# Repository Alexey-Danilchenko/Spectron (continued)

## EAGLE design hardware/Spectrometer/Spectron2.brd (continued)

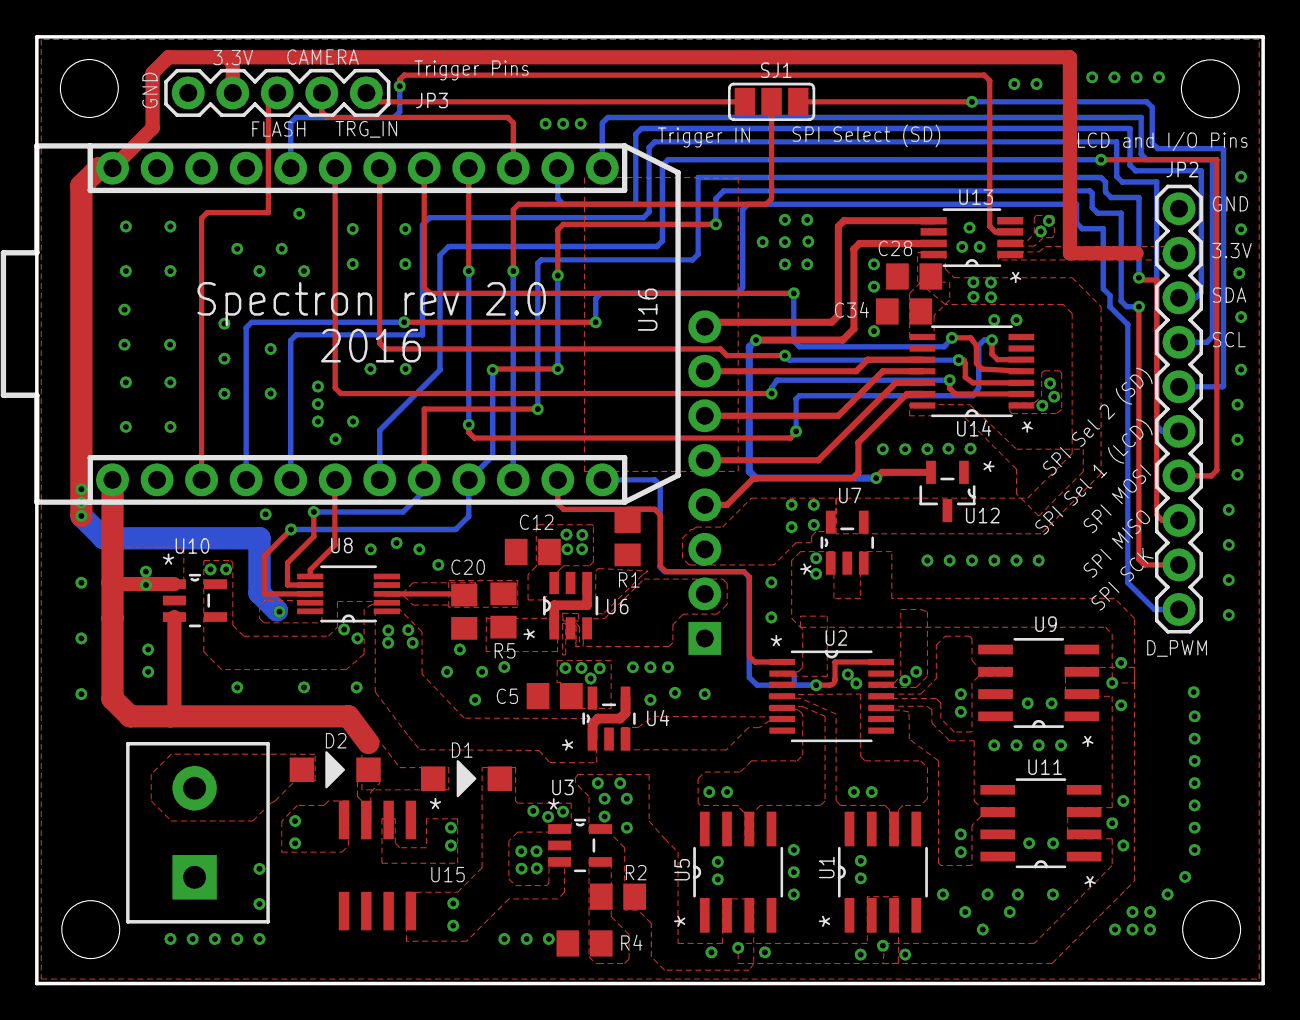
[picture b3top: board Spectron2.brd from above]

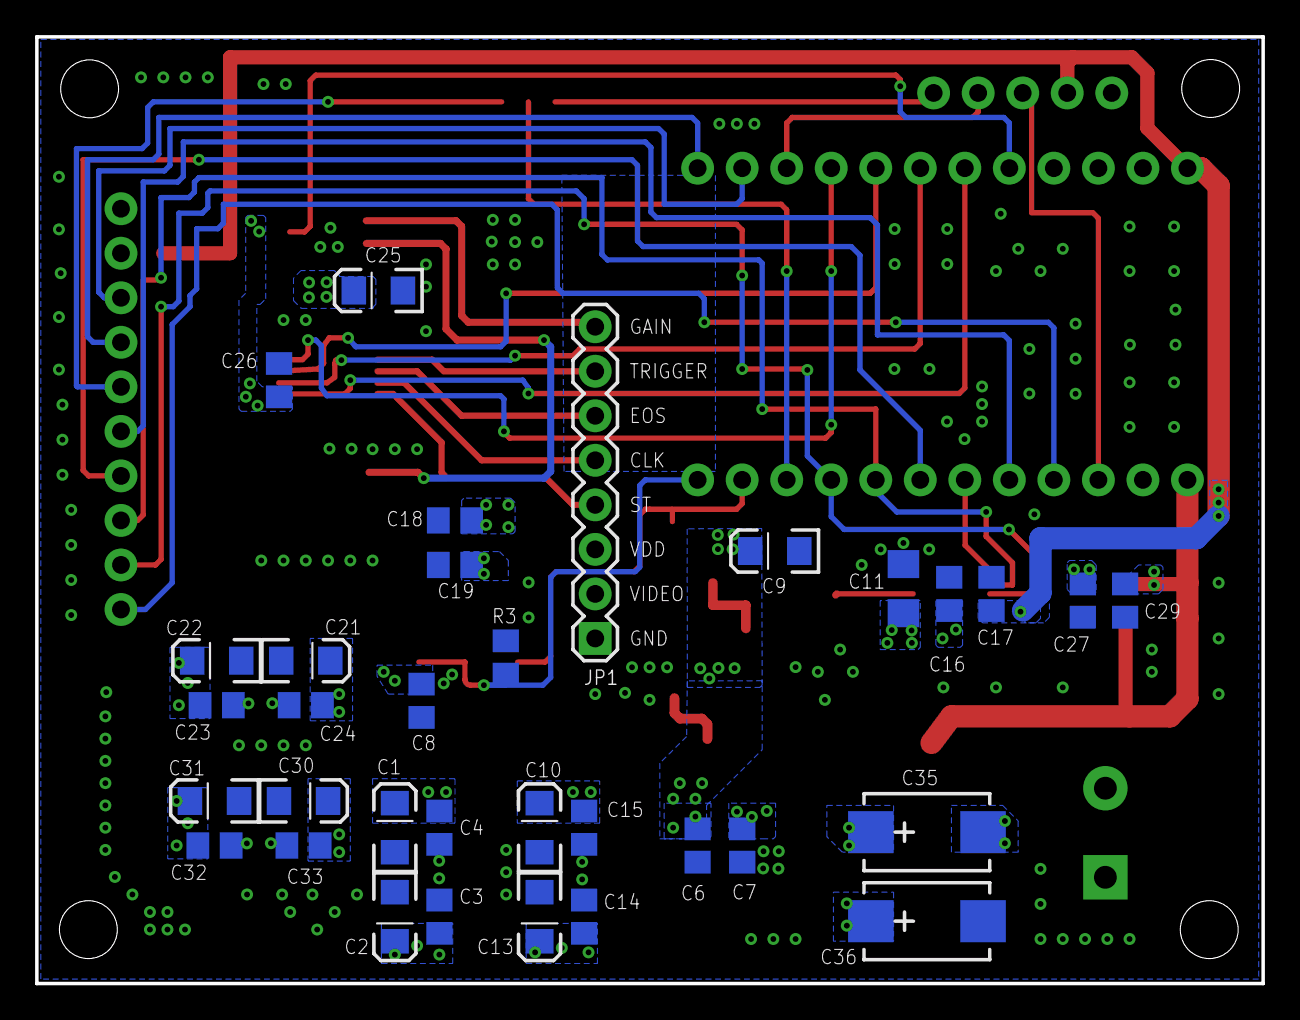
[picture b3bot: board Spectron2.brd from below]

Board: 2 copper layers, 70.0 x 54.0 mm, 69 parts (33 on the bottom side), 47 nets.

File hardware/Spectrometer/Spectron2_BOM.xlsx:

Qty | Value | Device | Package | Parts | Description | MPN | SUPPLIER | Distributor | Distributor Part Number
4 | 1uF | TANT-CAP1206 | EIA3216 | C1, C10, C21, C30 | Tantalum Capacitors - Solid SMD 1uF 25volts 10% A case Molded | 593D105X9025A2TE3 | Vishay | Mouser | 74-593D105X9025A2TE3
1 | 22uF | C-EUC0805 | C0805 | C11 | Multilayer Ceramic Capacitors MLCC - SMD/SMT 0805 22uF 25volts X5R 20% | GRM21BR61E226ME44L | Murata | Mouser | 81-GRM21BR61E226ME4L
6 | 10uF | C-EUC0805 | C0805 | C6, C7,C18, C19, C27, C29 | Multilayer Ceramic Capacitors MLCC - SMD/SMT 0805 10uF 35volts *Derate Voltage/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 | GRM21BC71E106KE11L | Murata | Mouser | 81-GRM21BC8YA106KE1L
1 | 2.7 nF | C-EUC0805 | C0805 | C20 | Multilayer Ceramic Capacitors MLCC - SMD/SMT 0805 2700pF 25volt X7R +/-10% | GRM216R71E272KA01D | Murata | Mouser | 81-GRM216R71E272KA1D
17 | 0.1uF | C-EUC0805 | C0805 | C3, C4, C8, C12, C14, C15, C16, C17, C23, C24, C26, C28, C32, C33, C34 and C1, 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 | Multilayer Ceramic Capacitors MLCC - SMD/SMT 0805 0.1uF 25volts X7R 10% | GRM21BR71E104KA01L | Murata | Mouser | 81-GRM40X104K25L
2 | 47uF | CPOL-USCT7343 | CT7343 | C35, C36 | Tantalum Capacitors - Polymer SMD 35volts 47uF 20% ESR=30mohms | T521X476M035ATE030 | Kemet | Mouser | 80-T521X476M35ATE30
1 | 1uF | C-EUC0805 | C0805 | C5 | Multilayer Ceramic Capacitors MLCC - SMD/SMT | GRM21BR71H105KA12K | Murata | Mouser | 81-GRM21BR71H105KA2K
6 | 10uF | TANT-CAP1206 | EIA3216 | C2, C9, C13, C22, C25, C31 | Tantalum Capacitors - Solid SMD 10UF 25V 10% | F951E106KAAAQ2 | AVX | Mouser | 647-F951E106KAAAQ2
2 | PMEG2010ER | DIODE-SOD123 | SOD123 | D1, D2 | Schottky Diodes & Rectifiers SCHOTTKY LOW VF | PMEG2010ER,115 | NXP | Mouser | 771-PMEG2010ER115
3 | 10K | R-EU_R0805 | R0805 | R1, R2, R3 | Thick Film Resistors - SMD 1/8watt 10Kohms 1% 100ppm | CRCW080510K0FKEA | Vishay | Mouser | 71-CRCW0805-10K-E3
1 | 20K | R-EU_R0805 | R0805 | R4 | Thick Film Resistors - SMD 1/8watt 20Kohms 1% 100ppm | CRCW080520K0FKEA | Vishay | Mouser | 71-CRCW0805-20K-E3
1 | 20 R | R-EU_R0805 | R0805 | R5 | Thick Film Resistors - SMD 0805 20ohm 1% Anti Surge AEC-Q200 | ESR10EZPF20R0 | ROHM Semiconductor | Mouser | 755-ESR10EZPF20R0
1 | AD7980 | AD7980 |  | U8 | Analog to Digital Converters - ADC 16-Bit 1 MSPS | AD7980ARMZ | Analog Devices | Mouser | 584-AD7980ARMZR7
1 | AD8031 | AD8031 |  | U4 | Operational Amplifiers - Op Amps 2.7V 800uA 80Mhz RRIO SGL | AD8031ARTZ-REEL7 | Analog Devices | Mouser | 584-AD8031ARTZ-R7
1 | ADA4841 | ADA4841 |  | U6 | Operational Amplifiers - Op Amps Low Power Low Noise and Distort RRO | ADA4841-1YRJZ-R7 | Analog Devices | Mouser | 584-ADA4841-1YRJZ-R7
1 | ADG1604 | ADG1604 |  | U2 | Multiplexer Switch ICs 4:1 19MHz 950 mOhm CMOS | ADG1604BRUZ | Analog Devices | Mouser | 584-ADG1604BRUZ-R7
1 | ADG3304 | ADG3304 |  | U14 | Translation - Voltage Levels Low VTG 1.15V-5.5V 4-CH Bidirect Logic | ADG3304BRUZ-REEL7 | Analog Devices | Mouser | 584-ADG3304BRUZ-R7
1 | ADG821 | ADG821 |  | U13 | Analogue Switch ICs 500mOhm 5.5V CMOS Dual SPST | ADG821BRMZ-REEL7 | Analog Devices | Mouser | 584-ADG821BRMZ-R7
1 | ADP7142-2.5 | ADP7142 |  | U10 | LDO Voltage Regulators 40V 200mA LDO 2.5Vo | ADP7142AUJZ-2.5-R7 | Analog Devices | Mouser | 584-ADP7142AUJZ2.5R7
2 | ADP7142-5.0 | ADP7142 |  | U3, U7 | LDO Voltage Regulators 40V 200mA LDO 5.0Vo | ADP7142AUJZ-5.0-R7 | Analog Devices | Mouser | 584-ADP7142AUJZ5.0R7
1 | LM2662 | LM2662 |  | U15 | Voltage Regulators - Switching Regulators Switched Capacitor Vtg Cnvtr | LM2662MX/NOPB | Texas Instruments | Mouser | 926-LM2662MX/NOPB
1 | REF192 | REF192 |  | U1 | Voltage References 2.5V Prec Micropwr LDO Low VRef | REF192GSZ | Analog Devices | Mouser | 584-REF192GSZ-R7
1 | REF193 | REF193 |  | U5 | Voltage References 3V Prec Micropwr LDO | REF193GSZ | Analog Devices | Mouser | 584-REF193GSZ
1 | REF195 | REF195 |  | U11 | Voltage References 5V Prec Micropwr LDO Low VRef | REF195GSZ | Analog Devices | Mouser | 584-REF195GSZ-R
1 | REF198 | REF198 |  | U9 | Voltage References 4.096V Prec Micropwr LDO Low VRef | REF198GSZ | Analog Devices | Mouser | 584-REF198GSZ-R
1 | TLV809 | TLV809 |  | U12 | Supervisory Circuits 3Pin Supply Vltg Sup | TLV809K33DBVR | Texas Instruments | Mouser | 595-TLV809K33DBVR
1 | C12666/C12880 | Preci-Dip 350-80-108-00-006101 |  | JP1 | Header 8 | 714-87-112-31-012101 | Preci-Dip | RS-Online | 702-0060
1 | Trigger Pins | M05PTH | 1X05 | JP3 | Header 5
1 | POWERSUPPLY DC21MMX | POWERSUPPLY DC21MMX | POWERSUPPLY_DC-21MM | DC1 | DC Power Connectors Power Jacks | PJ-102AH | CUI Inc. | Mouser | 490-PJ-102AH
1 | PHOTON without headers | PHOTON without headers | PHOTON | U16 |  |  |  | Mouser
4 | Photon socket, sensor board socket | Preci-Dip 714-87-112-31-012101 |  |  |  | 714-87-112-31-012101 | Preci-Dip | DIGIKEY | 1212-1166-ND
2 | Photon headers for the sockets above | Preci-Dip 350-80-112-00-006101 |  |  |  | 350-80-112-00-006101, 350-PP-1NN-00-006101 series | Preci-Dip | RS-Online | 702-0095
1 | Spectrometer stand | MICRO SPECTROMETER |  |  | Hamamatsu Micro-Spectrometer C12666MA or C12880MA, part ordered is Preci-Dip st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 | 115-87-314-41-003101 | Preci-Dip | DIGIKEY | 1212-1045-ND

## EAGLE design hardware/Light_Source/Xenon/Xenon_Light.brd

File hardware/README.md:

# Hardware

All the custom made circuits and boards were designed in [Cadsoft Eagle](http://www.autodesk.com/products/eagle/overview). All components for these were separated into standalone Eagle library for easier access. 

__Note:__ All the boards were tuned up for making with [OSH Park](https://oshpark.com/) - all relevant DRC and ERC rule checks were therefore applied an validated.

This project has the following several distinct and standalone components:

* [Spectrometer](Spectrometer) - board controlling spectrometer and performing spectral measurements
* [Stepper Motor Control](Motor) - board driving stepper motor for automating monochromator operation
* [Light Sources](Light_Source) - selection of controllable light sources providing input for monochromator

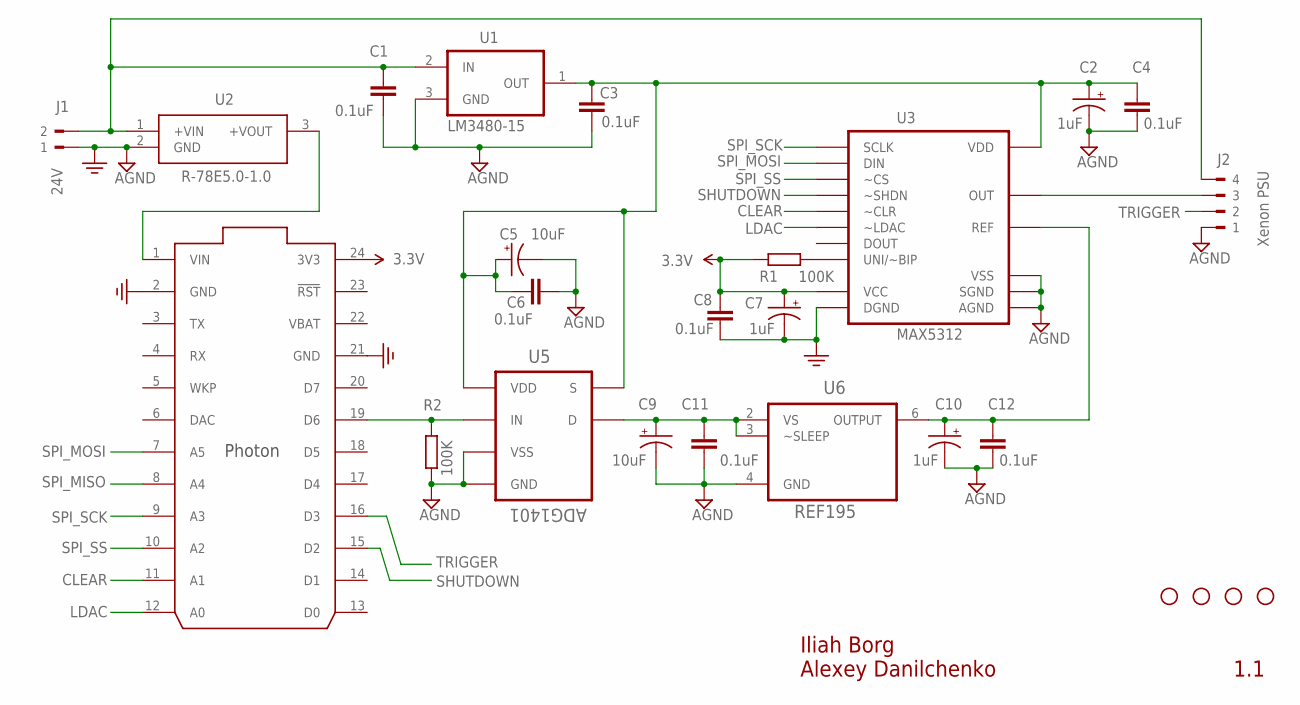
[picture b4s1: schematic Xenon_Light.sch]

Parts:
C1, C3, C4, C6, C8, C11, C12: 0.1uF; C0805
C2, C7, C10: 1uF; EIA3216
C5, C9: 10uF; EIA3216
J1: 24V; WEIDMULLER_PM5.08_2
J2: Xenon PSU; TERMINAL_BLK_4X5MM
R1, R2: 100K; R0805
STANDOFF1, STANDOFF2, STANDOFF3, STANDOFF4: STAND-OFF
U1: LM3480-15; SOT23
U2: R-78E5.0-1.0
U3: MAX5312; SSOP16
U4: PHOTON_WITH_HEADERS; PHOTON
U5: ADG1401; SOP65P490X110-8N
U6: REF195; SOIC127P600X175-8N

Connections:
3.3V: C7.A (+), C8.2, R1.2, U3.6 (VCC), U4.24 (3V3)
15V: C9.A (+), C11.2, U5.8 (D), U6.2 (VS), U6.3 (~SLEEP)
CLEAR: U3.15 (~CLR), U4.11 (A1)
GND: C1.1, C2.C (-), C3.1, C4.1, C5.C (-), C6.1, C7.C (-), C8.1, C9.C (-), C10.C (-), C11.1, C12.1, J1.1, J2.1, R2.1, U1.3 (GND), U2.2 (GND), U3.5 (DGND), U3.10 (SGND), U3.11 (AGND), U3.12 (VSS), U4.2 (GND), U4.21 (GND), U5.3 (GND), U5.7 (VSS), U6.4 (GND)
LDAC: U3.16 (~LDAC), U4.12 (A0)
unnamed: C1.2, J1.2, J2.4, U1.2 (IN), U2.1 (+VIN)
unnamed: U2.3 (+VOUT), U4.1 (VIN)
unnamed: R2.2, U4.19 (D6), U5.6 (IN)
unnamed: R1.1, U3.8 (UNI/~BIP)
unnamed: J2.3, U3.9 (OUT)
REF: C10.A (+), C12.2, U3.13 (REF), U6.6 (OUTPUT)
SHUTDOWN: U3.7 (~SHDN), U4.15 (D2)
SPI_MISO: U4.8 (A4)
SPI_MOSI: U3.2 (DIN), U4.7 (A5)
SPI_SCK: U3.1 (SCLK), U4.9 (A3)
SPI_SS: U3.3 (~CS), U4.10 (A2)
TRIGGER: J2.2, U4.16 (D3)
V15V: C2.A (+), C3.2, C4.2, C5.A (+), C6.2, U1.1 (OUT), U3.14 (VDD), U5.1 (S), U5.4 (VDD)
VBAT: U4.22 (VBAT)

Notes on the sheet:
1.1
Iliah Borg Alexey Danilchenko

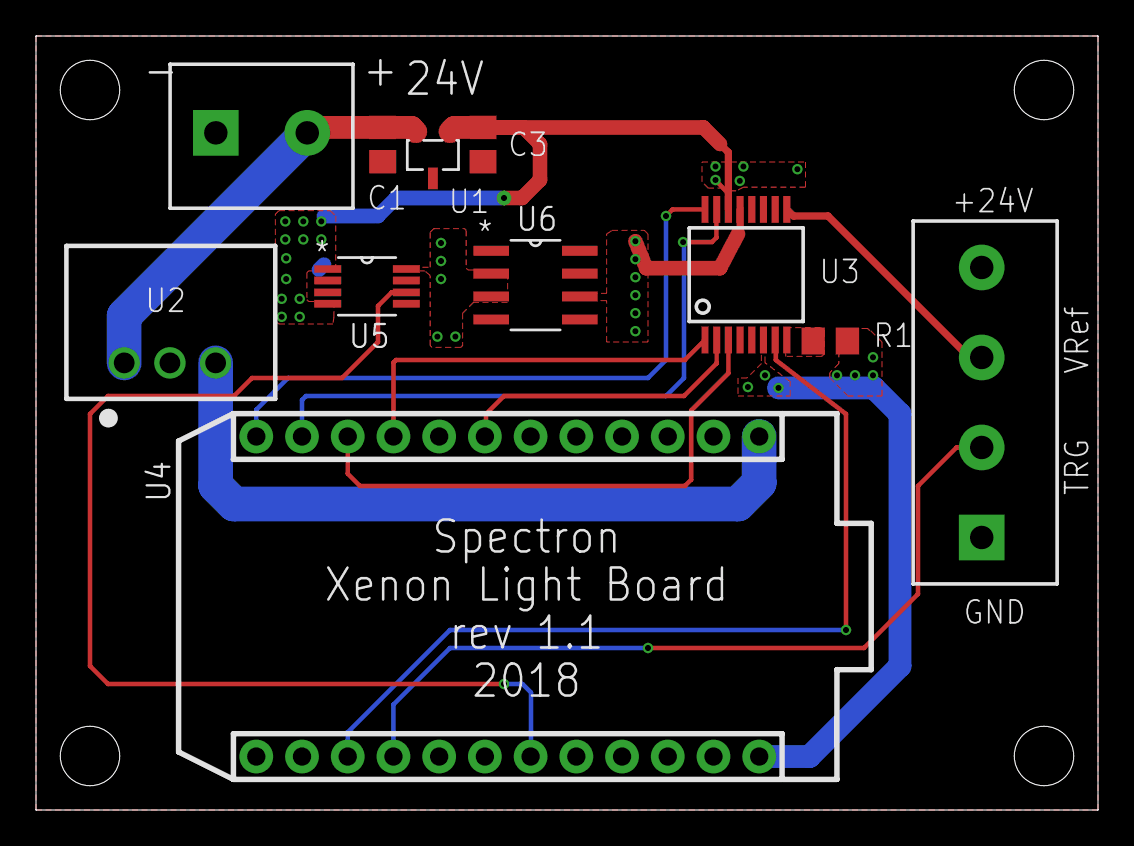
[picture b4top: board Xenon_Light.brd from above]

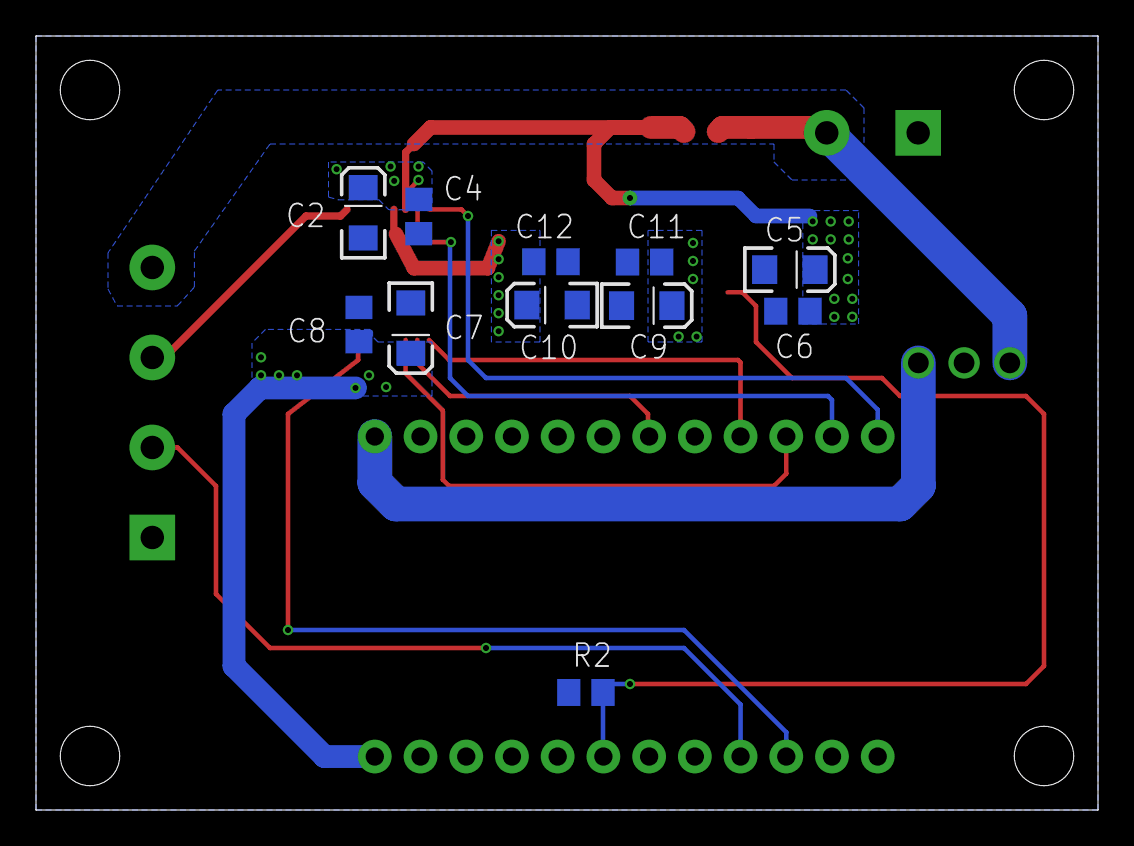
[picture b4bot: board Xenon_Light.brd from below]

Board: 2 copper layers, 59.0 x 43.0 mm, 26 parts (11 on the bottom side), 17 nets.

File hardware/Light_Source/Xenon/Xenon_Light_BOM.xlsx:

Qty | Value | Device | Package | Parts | Description | MPN | SUPPLIER | Distributor | Distributor Part Number
3 | 1uF | TANT-CAP1206 | EIA3216 | C2, C7, C10 | Tantalum Capacitors - Solid SMD 1uF 35V 20% A case | TMCMA1V105MTRF | Vishay | Mouser | 74-TMCMA1V105MTRF
7 | 0.1uF | C-EUC0805 | C0805 | C1,C3,C4,C6,C8,C11,C12 | Multilayer Ceramic Capacitors MLCC - SMD/SMT CEU 0805 50V 0.1uF X7R 10% | CEU4J2X7R1H104K125AE | TDK | Mouser | 810-CEU4J2X7R1H104K
2 | 10uF | TANT-CAP1206 | EIA3216 | C5,C9 | Tantalum Capacitors - Solid SMD 25V 10uF 20% 1206 ESR= 2 Ohms | F951E106MAAAQ2 | AVX | Mouser | 647-F951E106MAAAQ2
2 | 100K | R-EU_R0805 | R0805 | R1, R2 | Thick Film Resistors - SMD Thick Film Resistors - SMD 0805 100Kohms 5% AEC-Q200 | ERJ-6GEYJ104V | Panasonic | Mouser | 667-ERJ-6GEYJ104V
1 | LM3480-15 | LM3480 | SOT23 | U1 | LDO Voltage Regulators 100mA Quasi LDO Linear Vtg Reg | LM3480IM3X-15/NOPB | Texas Instruments | Mouser | 926-LM3480IM3X15NOPB
1 | R-78E5.0-1.0 | R-78E5.0-1.0 | R-78E5.0-1.0 | U2 | Non-Isolated DC/DC Converters 8-28Vin 5V 1.0A THRU | R-78E5.0-1.0 | RECOM Power | Mouser | 919-R-78E5.0-1.0
1 | MAX5312 | MAX5312 | SSOP16 | U3 | Digital to Analog Converters - DAC 12-Bit Precision DAC | MAX5312EAE+ | Maxim Integrated | Mouser | 700-MAX5312EAE
1 | ADG1401 | ADG1401BRMZ | SOP65P490X110-8N | U5 | Analogue Switch ICs IC 1 Ohm 16.5V iCMOS SPST | ADG1401BRMZ | Analog Devices | Mouser | 584-ADG1401BRMZ
1 | REF195 | REF195 | SOIC127P600X175-8N | U6 | Voltage References 5V Prec Micropwr LDO Low VRef | REF195GSZ | Analog Devices | Mouser | 584-REF195GSZ-R
1 | PHOTON without headers | PHOTON without headers | PHOTON | U4 |  |  |  | Mouser
2 | Photon socket | Preci-Dip 714-87-112-31-012101 |  |  |  | 714-87-112-31-012101 | Preci-Dip | DIGIKEY | 1212-1166-ND
2 | Photon headers for the sockets above | Preci-Dip 350-80-112-00-006101 |  |  |  | 350-80-112-00-006101, 350-PP-1NN-00-006101 series | Preci-Dip | RS-Online | 702-0095
1 | Xenon PSU | Terminal Block |  | J2 | 5mm Pitch Straight, PCB Terminal Block, PCB Mount, 4 Way | 897-0856 | RS Pro | RS-Online | 897-0856
1 | +24V | Terminal Block |  | J1 | 5mm Pitch Straight, PCB Terminal Block, PCB Mount, 2 Way | 282836-2 | TE Connectivity | RS-Online | 361-7667

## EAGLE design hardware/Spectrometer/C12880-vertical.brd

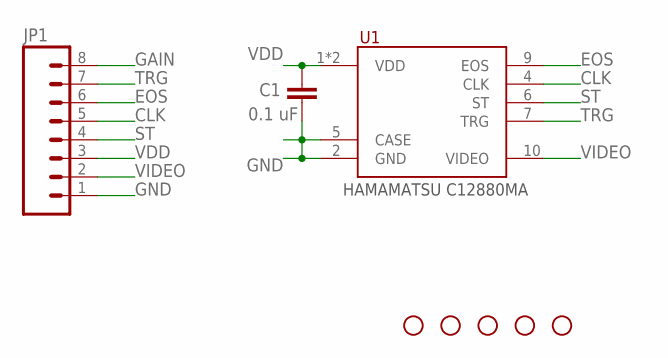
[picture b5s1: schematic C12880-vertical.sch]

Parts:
C1: 0.1 uF; C0805
JP1: M08SILK_FEMALE_PTH; 1X08
STANDOFF1, STANDOFF2, STANDOFF3, STANDOFF4, STANDOFF5: STAND-OFF
U1: MICROSPEC-C12880MA; C12880MA

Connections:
CLK: JP1.5, U1.4 (CLK)
EOS: JP1.6, U1.9 (EOS)
GAIN: JP1.8
GND: C1.2, JP1.1, U1.2 (GND), U1.5 (CASE)
ST: JP1.4, U1.6 (ST)
TRG: JP1.7, U1.7 (TRG)
VDD: C1.1, JP1.3, U1.1 (VDD), U1.3 (VDD)
VIDEO: JP1.2, U1.10 (VIDEO)

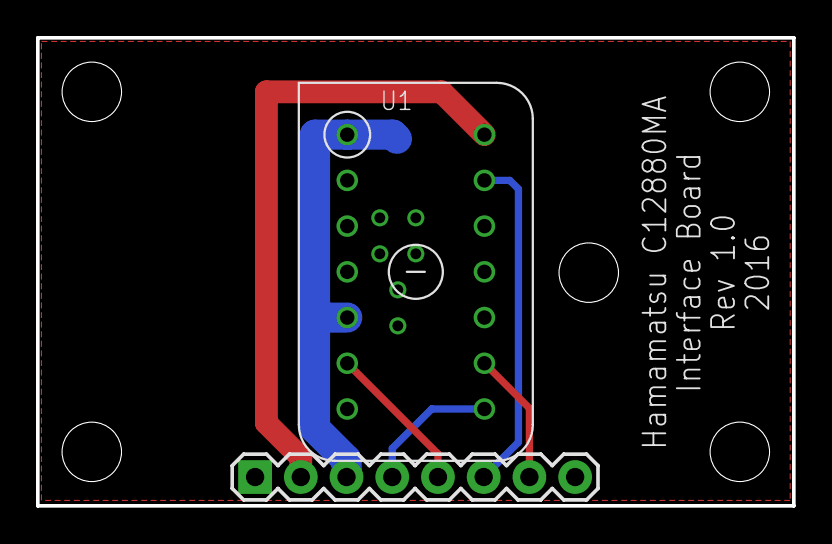
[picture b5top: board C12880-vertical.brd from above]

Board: 2 copper layers, 42.0 x 26.0 mm, 8 parts (1 on the bottom side), 7 nets.

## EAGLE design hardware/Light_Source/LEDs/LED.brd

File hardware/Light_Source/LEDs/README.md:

# LED Light Source

The LED light source component uses [Yuji LEDs](https://store.yujiintl.com/). More specifically their VTC (CRI 98) LEDs in [COB package for 5600K](YJWJ040-1.0_YJ-VTC-135L-G01.pdf) correlated colour temperature. A package of 4xVTC LED COBs clustered together is used for this light source. For more technical details on individual COB specifications see [Yuji LED web store](https://store.yujiintl.com/collections/led-cobs/products/yujileds-cri-98-9w-cob-led-135l).

These LEDs were chosen for the broad spectrum coverage they provide. An example of spectral response captured from the LEDs used in this setup ([also available as .CSV file](VTC5600_spectrum.csv)):

This component consists of two distinct and connected parts - LED driver/controller board and LED light head assembly. The whole circuit requires +12V/5A DC power supply to operate.

The photo below gives a clearer idea of the asssembled setup:

### LED Driver Board

The LED driver/controller board is a standalone LED driver with PWM control and 4000:1 dimming ratios (programmatically controlled). The LED driver board has two constant current channels - each capable of driving 450mA LEDs with up to 50V. This setup uses 2x LED strings (one per each channels) with 2xLEDs in series in each string (4x LEDs in total).

The board has 4 pin PWM connector allowing to control LED heatsink fan (if it is used). It also features I2C temperature sensor connector for board/environment temperature monitoring (if used) and 1-Wire thermocouple interface connector for LED temperature monitoring (if used).

Board schematic is also [available as standalone PDF](LED.pdf). Bill of material [is available in Excel format](LED_BOM.xlsx).

The following are the board layouts available (generated by OSH Park preview):

### LED Light Head Assembly

This assembly utilises the board with connector to the main LED driver board and mechanical connectors to 4xVTC LED COBs mounted directly on heatsink. The board has square cutout that fits tightly around 2x2 layout of VTC LED COBs with metallic pins soldered to the board acting as mechanical connectors to the LEDs. This allows to keep LEDs and heatsink setup separate from the board and optical assembly for easier replacement of the parts. The LED COBs are connected in series of two per string. 

The LED COBs are glued to a heatsink directly with [Arctic Silver Thermal Adhesive](http://www.arcticsilver.com/arctic_silver_thermal_adhesive.htm) in a tightly formed cluster. In series connection for each pair is formed by direct wire soldering onto the LEDs. This photo illustrates the setup:

The board with soldered pins on top of LEDs mounted on heatsink as follows:

The board then has a range of holes to allow attachments of the reflector, condenser lens and holder. Below is the example of the fully assembled setup:

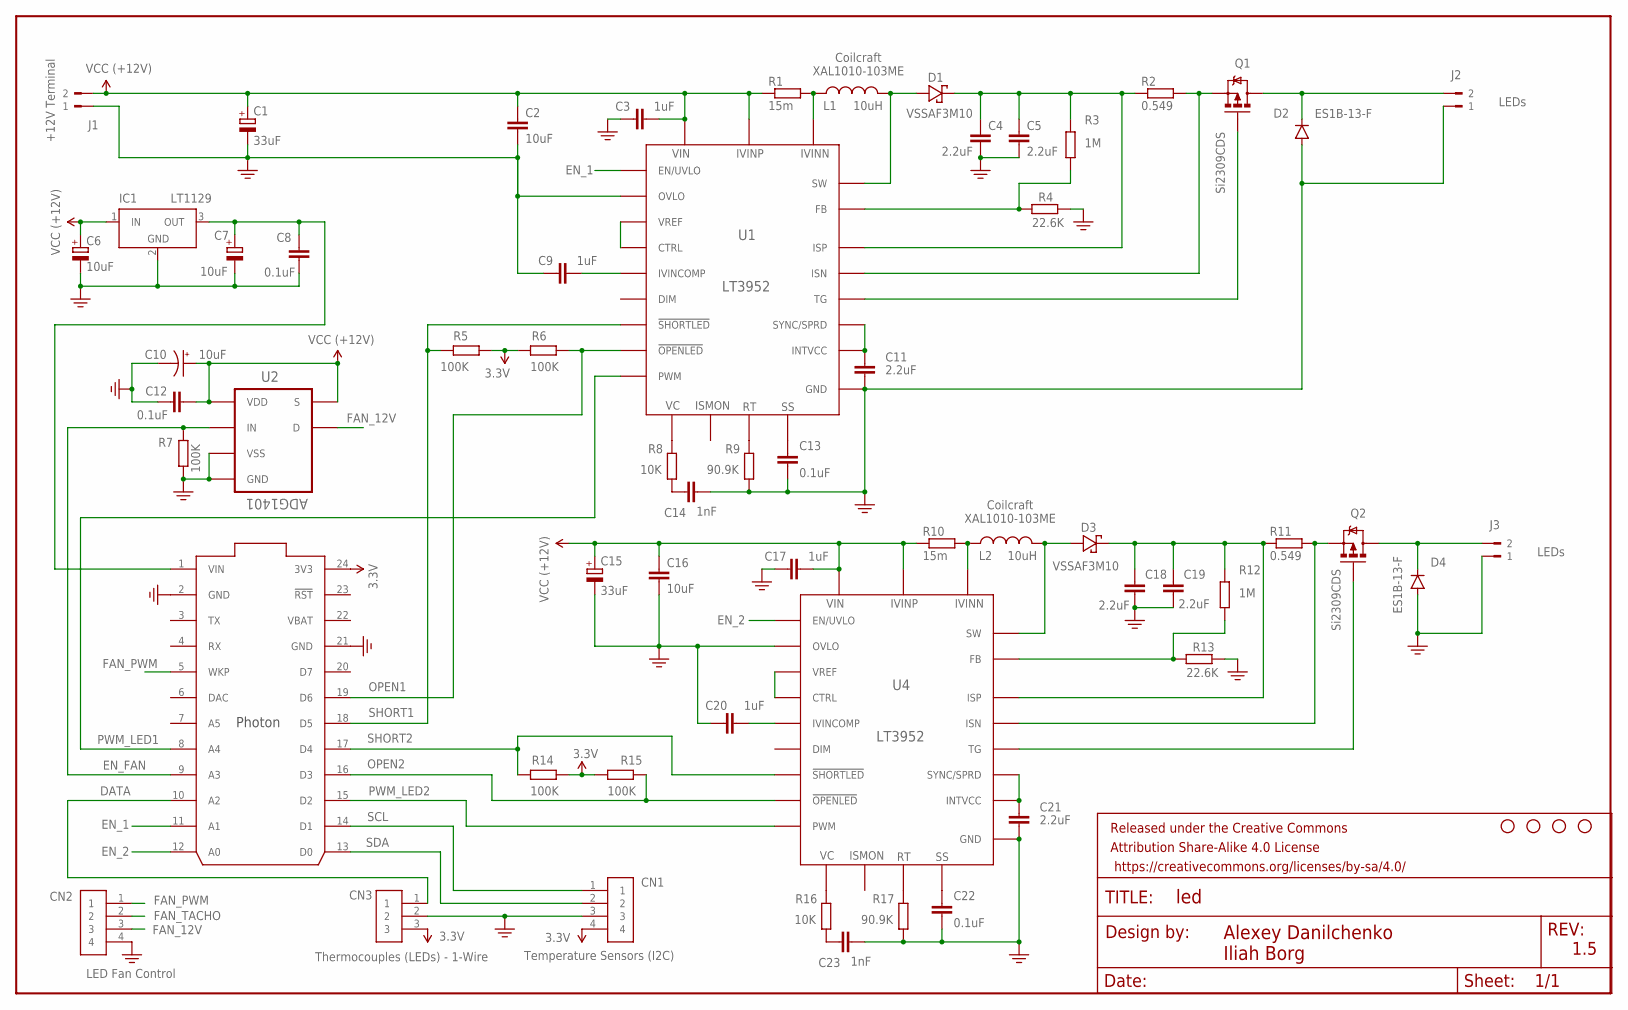
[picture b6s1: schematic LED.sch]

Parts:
C1, C15: 33uF; PANASONIC_E
C2, C16: 10uF; C1206
C3, C9, C17, C20: 1uF; C0805
C4, C5, C18, C19: 2.2uF; C1206
C6, C7: 10uF; CT7343
C8, C12, C13, C22: 0.1uF; C0805
C10: 10uF; EIA3216
C11, C21: 2.2uF; C0805
C14, C23: 1nF; C0805
CN1: Temperature Sensors (I2C); 1X04-BIG
CN2: LED Fan Control; 1X04-BIG
CN3: Thermocouples (LEDs) - 1-Wire; 1X03
D1, D3: VSSAF3M10; SODFL5226X100N
D2, D4: ES1B-13-F; SMA-DIODE_ALT
FRAME1: 1.0; CREATIVE_COMMONS
IC1: LT1129; SOT223
J1: +12V Terminal; WEIDMULLER_PM5.08_2
J2, J3: LEDs; WEIDMULLER_PM5.08_2
L1, L2: 10uH; XAL1010
Q1, Q2: Si2309CDS; SOT23-3
R1, R10: 15m; R1206
R2, R11: 0.549; R1206
R3, R12: 1M; R0805
R4, R13: 22.6K; R0805
R5, R6, R7, R14, R15: 100K; R0805
R8, R16: 10K; R0805
R9, R17: 90.9K; R0805
STANDOFF1, STANDOFF2, STANDOFF3, STANDOFF4: STAND-OFF
U1, U4: LT3952; TSSOP-28_FE/EB-M
U2: ADG1401; SOP65P490X110-8N
U3: PHOTON_WITH_HEADERS; PHOTON

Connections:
3.3V: CN1.4, CN3.3, R5.1, R6.2, R14.2, R15.1, U3.24 (3V3)
+5VDC: C7.+, C8.1, IC1.3 (OUT), U3.1 (VIN)
DATA: CN3.1, U3.10 (A2)
EN_1: U1.8 (EN/UVLO), U3.11 (A1)
EN_2: U3.12 (A0), U4.8 (EN/UVLO)
EN_FAN: R7.2, U2.6 (IN), U3.9 (A3)
FAN_12V: CN2.3, U2.8 (D)
FAN_PWM: CN2.1, U3.5 (WKP)
FAN_TACHO: CN2.2
GND: C1.-, C2.2, C3.2, C4.2, C5.2, C6.-, C7.-, C8.2, C9.2, C10.C (-), C11.2, C12.1, C13.2, C14.2, C15.-, C16.2, C17.2, C18.2, C19.2, C20.2, C21.2, C22.2, C23.2, CN1.3, CN2.4, CN3.2, D2.A, D4.A, IC1.2 (GND), IC1.4 (GND), J1.1, J2.1, J3.1, R4.1, R7.1, R9.1, R13.1, R17.1, U1.1 (GND), U1.9 (OVLO), U1.12 (GND), U1.28 (GND), U1.EPAD (GND), U2.3 (GND), U2.7 (VSS), U3.2 (GND), U3.21 (GND), U4.1 (GND), U4.9 (OVLO), U4.12 (GND), U4.28 (GND), U4.EPAD (GND)
unnamed: L1.1, R1.2, U1.5 (IVINN)
unnamed: D1.2 (A), L1.2, U1.2 (SW), U1.3 (SW), U1.4 (SW)
unnamed: C4.1, C5.1, D1.1 (K), R2.1, R3.2, U1.27 (ISP)
unnamed: R3.1, R4.2, U1.16 (FB)
unnamed: D2.C, J2.2, Q1.3 (D)
unnamed: Q1.2 (S), R2.2, U1.26 (ISN)
unnamed: Q1.1 (G), U1.25 (TG)
unnamed: C11.1, U1.10 (INTVCC), U1.11 (SYNC/SPRD)
unnamed: U1.17 (CTRL), U1.18 (VREF)
unnamed: C9.1, U1.23 (IVINCOMP)
unnamed: R9.2, U1.14 (RT)
unnamed: C13.1, U1.19 (SS)
unnamed: C14.1, R8.1
unnamed: R8.2, U1.13 (VC)
unnamed: L2.1, R10.2, U4.5 (IVINN)
unnamed: D3.2 (A), L2.2, U4.2 (SW), U4.3 (SW), U4.4 (SW)
unnamed: C18.1, C19.1, D3.1 (K), R11.1, R12.2, U4.27 (ISP)
unnamed: D4.C, J3.2, Q2.3 (D)
unnamed: Q2.2 (S), R11.2, U4.26 (ISN)
unnamed: R12.1, R13.2, U4.16 (FB)
unnamed: Q2.1 (G), U4.25 (TG)
unnamed: C21.1, U4.10 (INTVCC), U4.11 (SYNC/SPRD)
unnamed: U4.17 (CTRL), U4.18 (VREF)
unnamed: C20.1, U4.23 (IVINCOMP)
unnamed: C22.1, U4.19 (SS)
unnamed: R17.2, U4.14 (RT)
unnamed: C23.1, R16.1
unnamed: R16.2, U4.13 (VC)
OPEN1: R6.1, U1.22 (!OPENLED), U3.19 (D6)
OPEN2: R15.2, U3.16 (D3), U4.22 (!OPENLED)
PWM_LED1: U1.20 (PWM), U3.8 (A4)
PWM_LED2: U3.15 (D2), U4.20 (PWM)
SCL: CN1.1, U3.14 (D1)
SDA: CN1.2, U3.13 (D0)
SHORT1: R5.2, U1.21 (!SHORTLED), U3.18 (D5)
SHORT2: R14.1, U3.17 (D4), U4.21 (!SHORTLED)
VBAT: U3.22 (VBAT)
VDD: C1.+, C2.1, C3.1, C6.+, C10.A (+), C12.2, C15.+, C16.1, C17.1, IC1.1 (IN), J1.2, R1.1, R10.1, U1.6 (IVINP), U1.7 (VIN), U2.1 (S), U2.4 (VDD), U4.6 (IVINP), U4.7 (VIN)

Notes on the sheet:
1.5
Coilcraft XAL1010-103ME

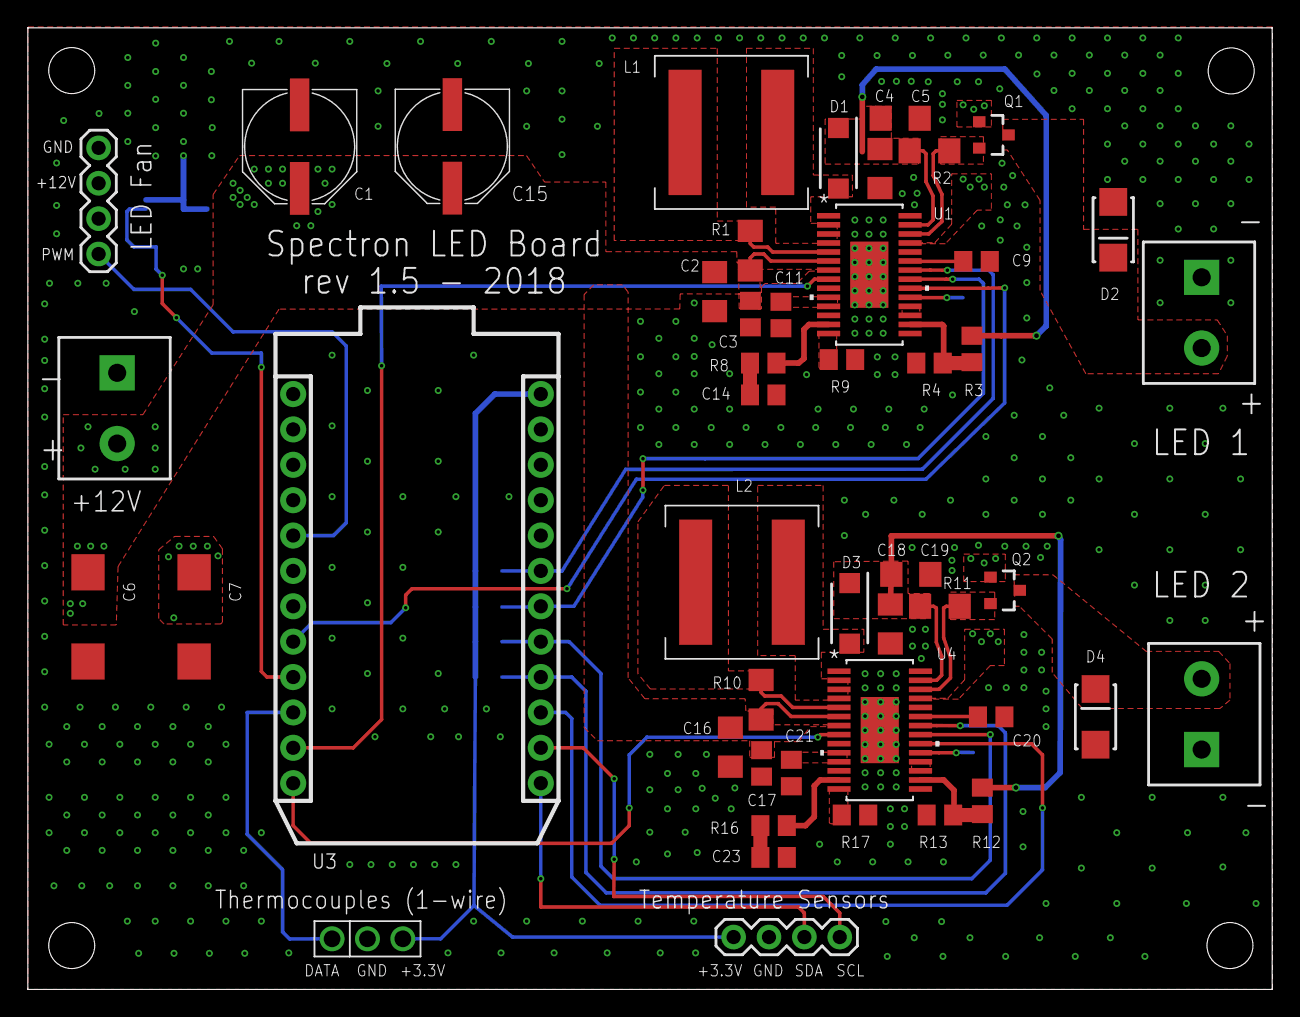
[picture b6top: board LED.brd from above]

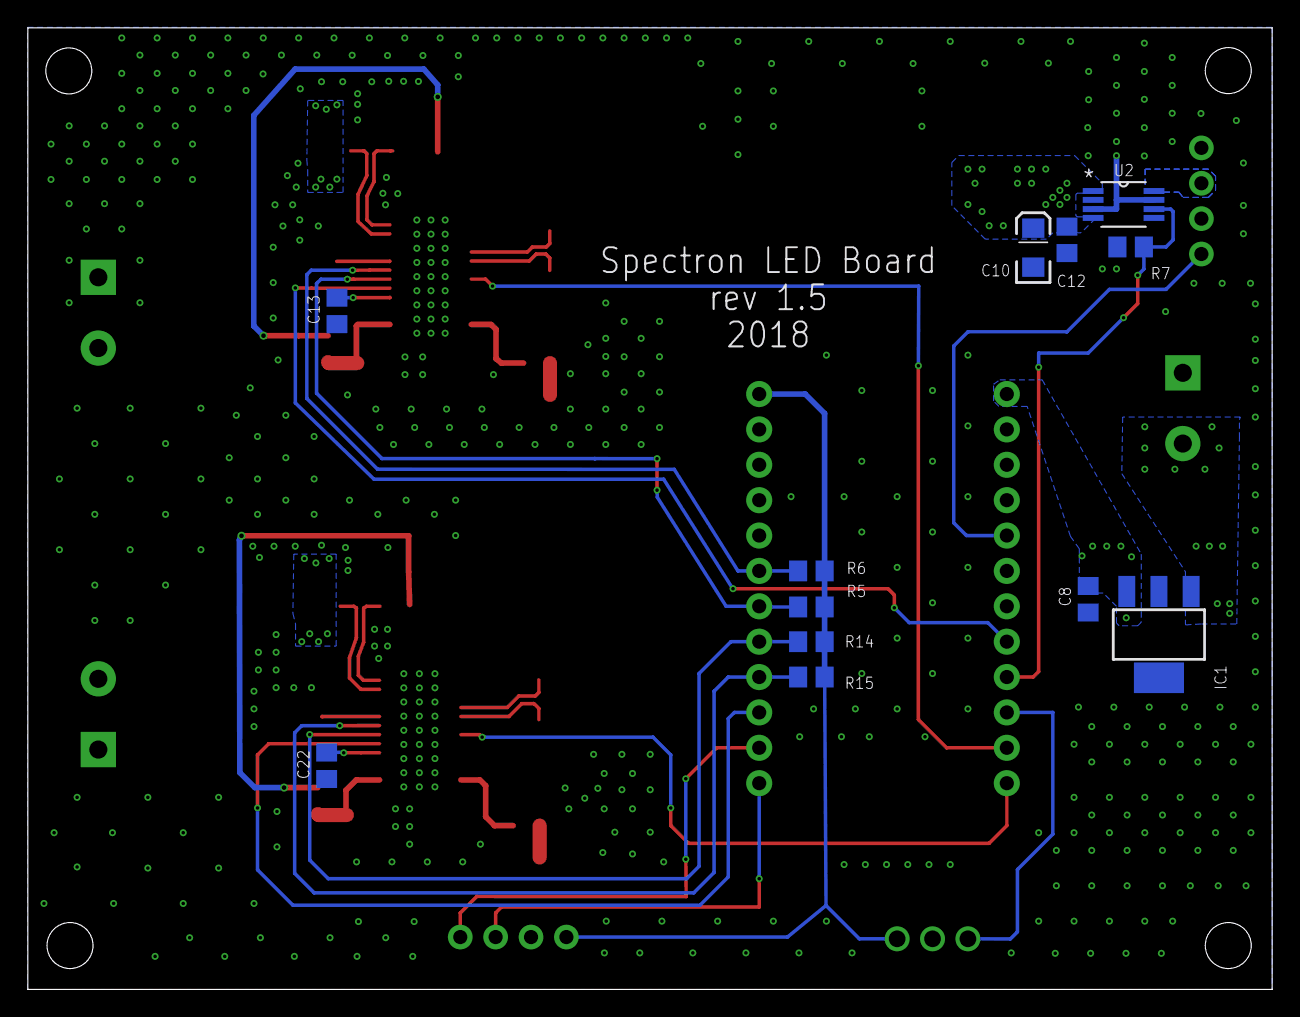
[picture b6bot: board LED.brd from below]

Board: 2 copper layers, 89.3 x 69.0 mm, 64 parts (12 on the bottom side), 46 nets.

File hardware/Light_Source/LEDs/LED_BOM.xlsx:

Qty | Value | Device | Package | Parts | Description | MPN | SUPPLIER | Distributor | Distributor Part Number
2 | 39uF | CPOL-EUE | PANASONIC_E | C1,C15 | Aluminium Polymer Capacitor 39μF 50V dc 8mm E12 OS-CON Series, Surface Mount Po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 | 50SVPF39M | Panasonic | RS-Online | 795-5427
2 | 10uF | C-EUC1206 | C1206 | C2,C16 | Multilayer Ceramic Capacitors MLCC - SMD/SMT SOFT 1206 35V 10uF X7R 20% | C3216X7R1V106M160AE | TDK | Mouser | 810-C3216X7R1V106M1E
4 | 1uF | C-EUC0805 | C0805 | C3,C9,C17,C20 | Multilayer Ceramic Capacitors MLCC - SMD/SMT SOFT 0805 50V 1uF X7R 20% | CGA4J3X7R1H105M125AE | TDK | Mouser | 810-CGA4J3X7R1H105MS
4 | 2.2uF | C-EUC1206 | C1206 | C4,C5,C18,C19 | Multilayer Ceramic Capacitors MLCC - SMD/SMT 1210 2.2uF 100volts X7R 20% | GCJ32DR72A225MA01L | Murata | Mouser | 81-GCJ32DR72A225M1L
2 | 10uF | CPOL-EUCT7343 | CT7343 | C6,C7 | Tantalum Capacitors - Polymer SMD 35V 10uF 2917 20% ESR=120mOhm AEC-Q200 | T591D106M035ATE120 | Kemet | Mouser | 80-T591D106M35ATE120
4 | 0.1uF | C-EUC0805 | C0805 | C8,C12,C13,C22 | Multilayer Ceramic Capacitors MLCC - SMD/SMT CEU 0805 50V 0.1uF X7R 10% | CEU4J2X7R1H104K125AE | TDK | Mouser | 810-CEU4J2X7R1H104K
1 | 10uF | TANT-CAP1206 | EIA3216 | C10 | Tantalum Capacitors - Solid SMD 25V 10uF 20% 1206 ESR= 2 Ohms | F951E106MAAAQ2 | AVX | Mouser | 647-F951E106MAAAQ2
2 | 2.2uF | C-EUC0805 | C0805 | C11,C21 | Multilayer Ceramic Capacitors MLCC - SMD/SMT SOFT 0805 50V 2.2uF X7R 20% | C2012X7R1H225M125AE | TDK | Mouser | 810-C2012X7R1H225M1E
2 | 1nF | C-EUC0805 | C0805 | C14,C23 | Multilayer Ceramic Capacitors MLCC - SMD/SMT WCAP-CSGP 1000pF 0805 10% 50V MLCC | 885012207086 | Wurth Electronics | Mouser | 710-885012207086
2 | 15m | R-EU_R1206 | R1206 | R1,R10 | Current Sense Resistors - SMD 0.5W 0.015 Ohm 1% | LVM12FTR015E-TR | Ohmite | Mouser | 588-LVM12FTR015E-TR
2 | 0.54900000000000004 | R-EU_R1206 | R1206 | R2,R11 | 588-LVM12FTR015E-TR | SR732BTTER549F | KOA Speer | Mouser | 660-SR732BTTER549F
2 | 1M | R-EU_R0805 | R0805 | R3,R12 | Thick Film Resistors - SMD 0805 1Mohms 1% Anti-Surge AEC-Q200 | ERJ-P6WF1004V | Panasonic | Mouser | 667-ERJ-P6WF1004V
2 | 22.6K | R-EU_R0805 | R0805 | R4,R13 | Thick Film Resistors - SMD 1/8watt 22.6Kohms 1% 100ppm | CRCW080522K6FKEA | Vishay | Mouser | 71-CRCW0805-22.6K-E3
2 | 10K | R-EU_R0805 | R0805 | R8,R16 | Thick Film Resistors - SMD 10kohms .25W 1% TCR100 RES SMD | CRS0805-FX-1002ELF | Bourns | Mouser | 652-CRS0805FX1002ELF
2 | 90.9K | R-EU_R0805 | R0805 | R9,R17 | Thick Film Resistors - SMD 0805 90.9Kohms 1% AEC-Q200 | ERJ-6ENF9092V | Panasonic | Mouser | 667-ERJ-6ENF9092V
5 | 100K | R-EU_R0805 | R0805 | R5,R6,R7,R14,R15 | Thick Film Resistors - SMD Thick Film Resistors - SMD 0805 100Kohms 5% AEC-Q200 | ERJ-6GEYJ104V | Panasonic | Mouser | 667-ERJ-6GEYJ104V
2 | VSSAF3M10 | VSSAF3M10-M3_H | SODFL5226X100N | D1,D3 | Schottky Diodes & Rectifiers TMBS 100V Vrrm eSMP SlimSMA (DO-221AC) | VSSAF3M10-M3/H | Vishay | Mouser | 78-VSSAF3M10-M3/H
2 | ES1B-13-F | DIODESMA-ALT | SMA-DIODE_ALT | D2,D4 | Rectifiers 100V 1A | ES1B-13-F | Diodes Incorporated | Mouser | 621-ES1B-F
2 | Si2309CDS | MOSFET-PCHANNEL | SOT23-3 | Q1,Q2 | MOSFET -60V Vds 20V Vgs SOT-23 | SI2309CDS-T1-GE3 | Vishay | Mouser | 781-SI2309CDS-GE3
2 | 10uH | XAL1010-103 | XAL1010 | L1,L2 | Fixed Inductors 10uH 20% 15.5A 14.75mOhms AEC-Q200 | XAL1010-103MED | Coilcraft | Mouser | 994-XAL1010-103MED
1 | LT1129 | LT1129CST5 | SOT223 | IC1 | LDO Voltage Regulators 700mA Micropower Low Dropout Regulator with Shutdown | LT1129CST-5#PBF | Linear Technology | Mouser | 584-LT1129CST-5#PBF
1 | LT3952 | LT3952EFEPBFTSSOP-28_FE/EB-M | TSSOP-28_FE/EB-M | U1,U4 | LED Lighting Drivers 60V LED Driver with 4A Switch Current | LT3952HFE#PBF | Linear Technology | Linear Technology | LT3952HFE#PBF
1 | ADG1401 | ADG1401BRMZ | SOP65P490X110-8N | U2 | Analogue Switch ICs IC 1 Ohm 16.5V iCMOS SPST | ADG1401BRMZ | Analog Devices | Mouser | 584-ADG1401BRMZ
1 | PHOTON without headers | PHOTON without headers | PHOTON | U3
2 | Photon socket | Preci-Dip 714-87-112-31-012101 |  |  |  | 714-87-112-31-012101 | Preci-Dip | DIGIKEY | 1212-1166-ND
2 | Photon headers for the sockets above | Preci-Dip 350-80-112-00-006101 |  |  |  | 350-80-112-00-006101, 350-PP-1NN-00-006101 series | Preci-Dip | RS-Online | 702-0095
3 | +12V,LED Outputs | Terminal Block |  | J1,J2,J3 | 5mm Pitch Straight, PCB Terminal Block, PCB Mount, 2 Way | 282836-2 | TE Connectivity | RS-Online | 361-7667

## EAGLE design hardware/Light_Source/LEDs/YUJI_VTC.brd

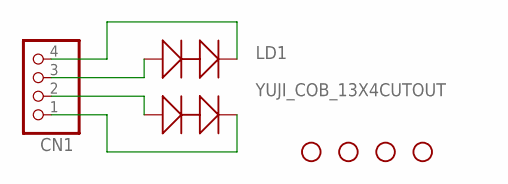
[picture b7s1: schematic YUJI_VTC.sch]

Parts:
CN1: JST_4PIN; JSTPH4
LD1: YUJI_COB_13X4CUTOUT; YUJI_COB_13X4_CUTOUT
STANDOFF1, STANDOFF2, STANDOFF3, STANDOFF4: STAND-OFF

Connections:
unnamed: CN1.3, LD1.ANODE1
unnamed: CN1.4, LD1.CATHODE1
unnamed: CN1.1, LD1.CATHODE2
unnamed: CN1.2, LD1.ANODE2
